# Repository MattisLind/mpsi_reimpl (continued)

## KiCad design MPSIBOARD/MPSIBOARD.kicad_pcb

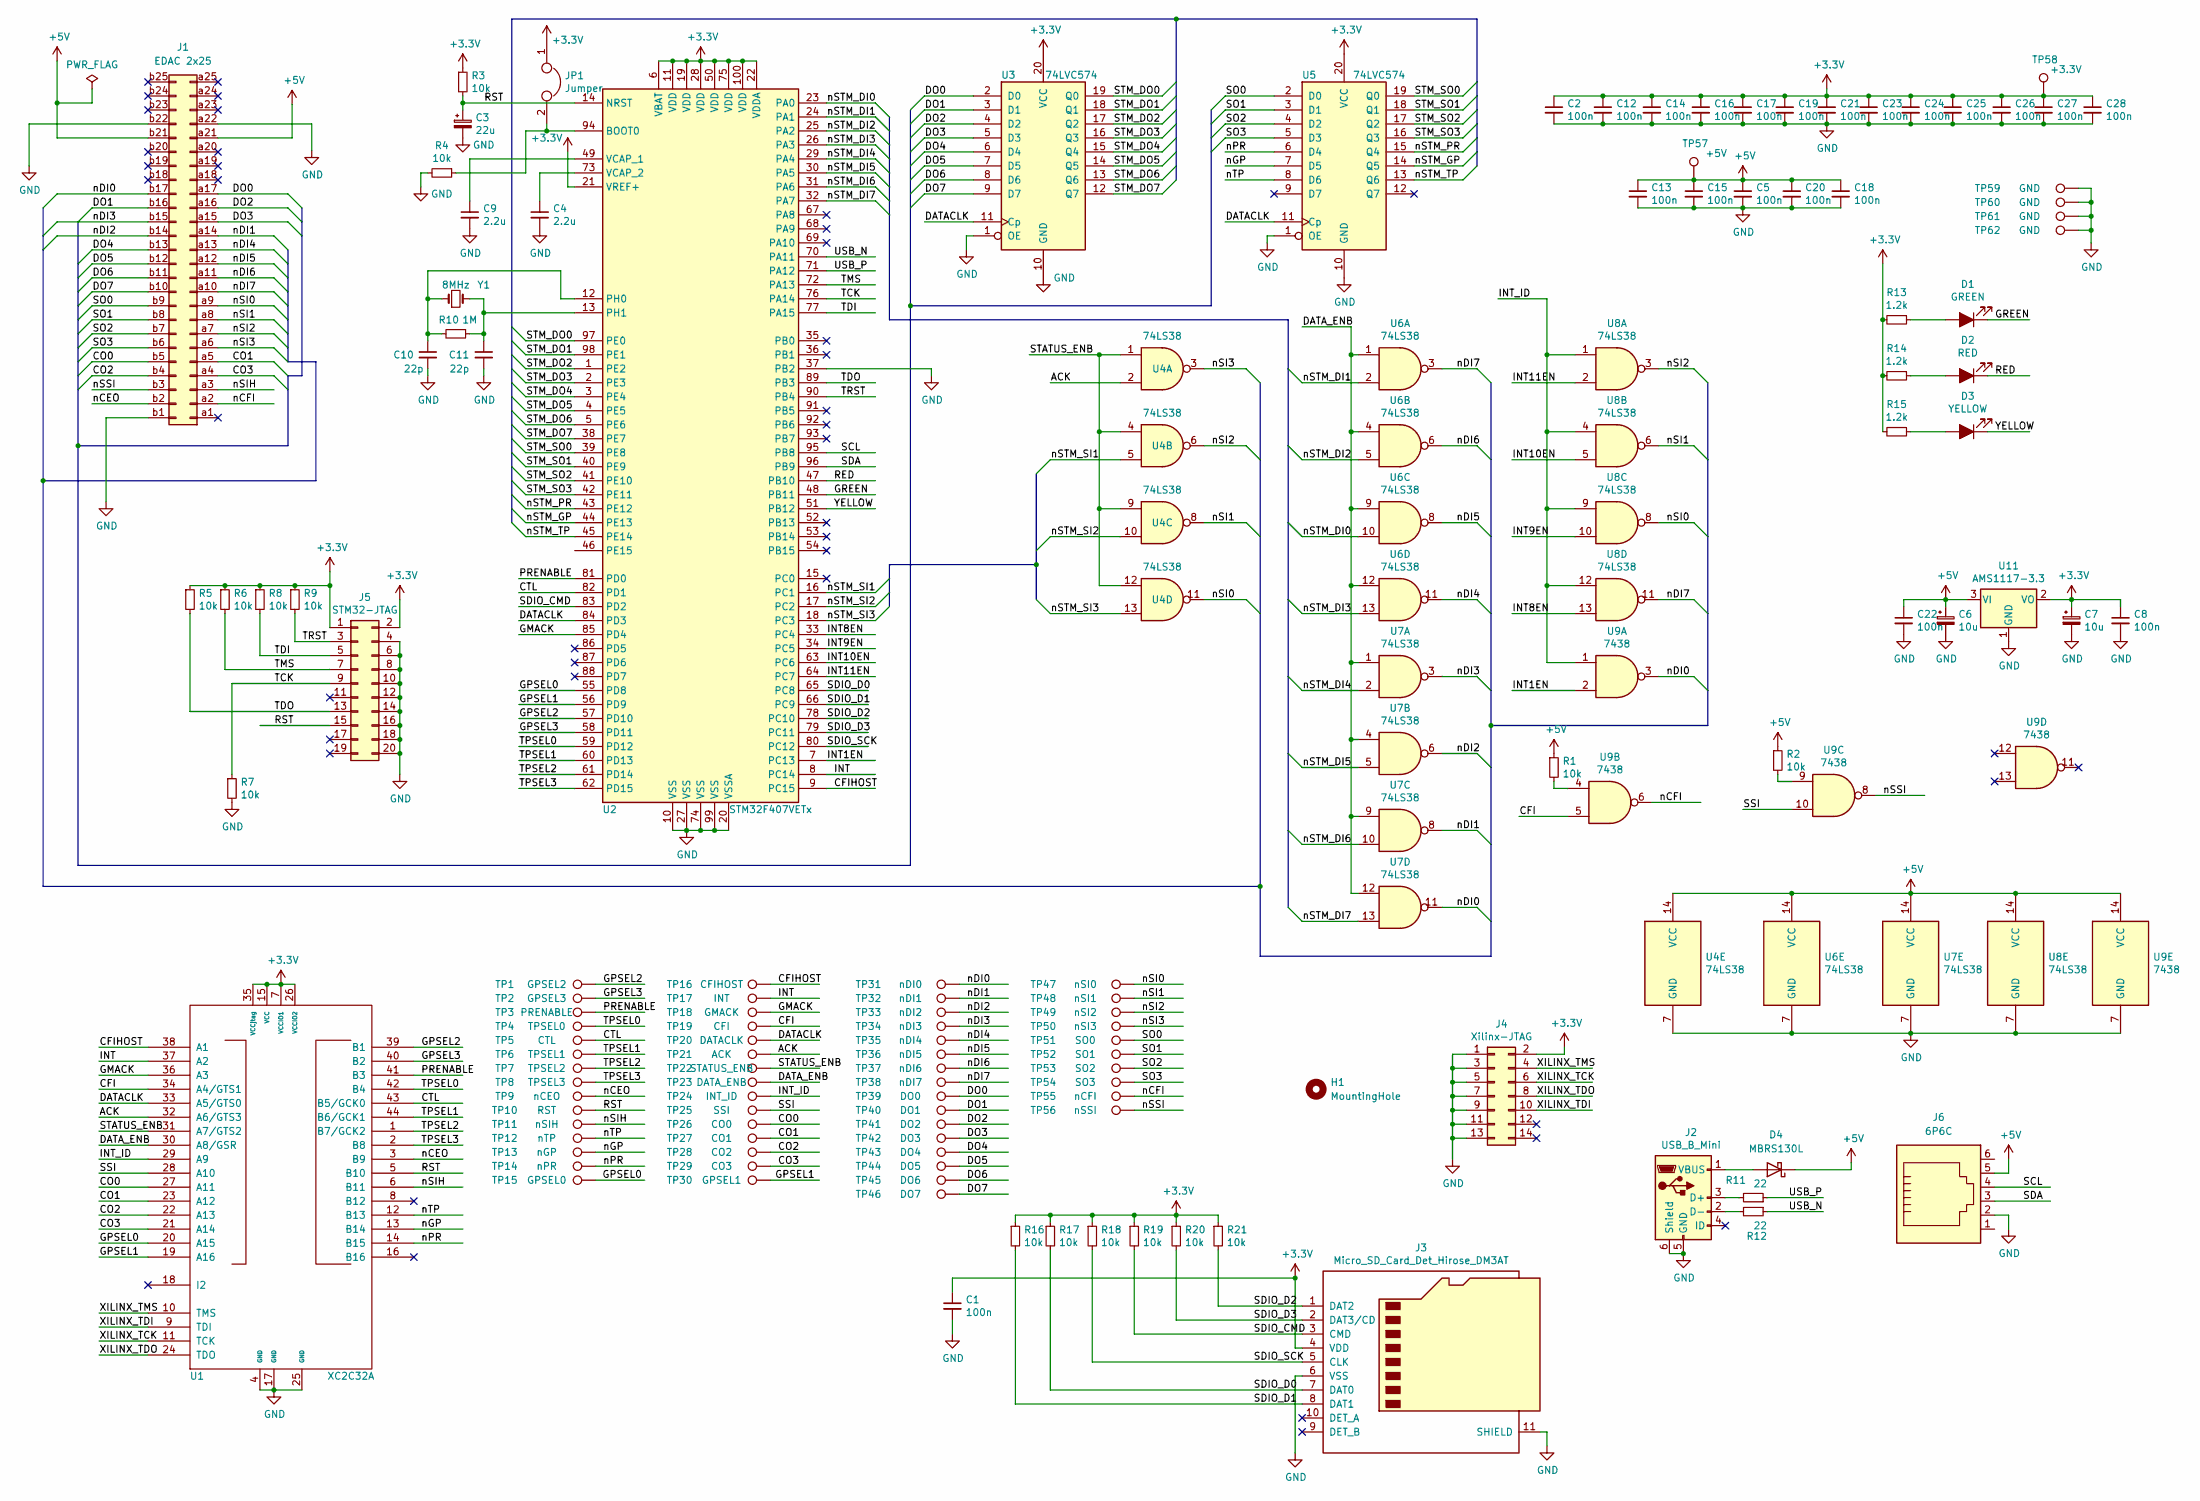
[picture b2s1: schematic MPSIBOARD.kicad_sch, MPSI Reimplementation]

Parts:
C1, C2, C5, C8, C12, C13, C14, C15, C16, C17, C18, C19, C20, C21, C22, C23, C24, C25, C26, C27, C28: 100n; C_0805_2012Metric
C3: 22u; CP_Elec_5x4.4
C4, C9: 2.2u; C_0805_2012Metric
C6, C7: 10u; CP_Elec_4x5.3
C10, C11: 22p; C_0805_2012Metric
D1: GREEN; LED_0805_2012Metric
D2: RED; LED_0805_2012Metric
D3: YELLOW; LED_0805_2012Metric
D4: MBRS130L; D_SMB
H1: MountingHole; MountingHole_3.2mm_M3
J1: EDAC 2x25; EDAC 2x25 3.96mm
J2: USB_B_Mini; USB_Mini-B_Lumberg_2486_01_Horizontal
J3: Micro_SD_Card_Det_Hirose_DM3AT; microSD_HC_Hirose_DM3AT-SF-PEJM5
J4: Xilinx-JTAG; IDC-Header_2x07_P2.54mm_Vertical
J5: STM32-JTAG; IDC-Header_2x10_P2.54mm_Vertical
J6: 6P6C; RJ12_Amphenol_54601
JP1: Jumper; PinHeader_1x02_P2.54mm_Vertical
R1, R2, R3, R4, R5, R6, R7, R8, R9, R16, R17, R18, R19, R20, R21: 10k; R_0805_2012Metric
R10: 1M; R_0805_2012Metric
R11, R12: 22; R_0805_2012Metric
R13, R14, R15: 1.2k; R_0805_2012Metric
TP1: GPSEL2; PinHeader_1x01_P2.54mm_Vertical
TP2: GPSEL3; PinHeader_1x01_P2.54mm_Vertical
TP3: PRENABLE; PinHeader_1x01_P2.54mm_Vertical
TP4: TPSEL0; PinHeader_1x01_P2.54mm_Vertical
TP5: CTL; PinHeader_1x01_P2.54mm_Vertical
TP6: TPSEL1; PinHeader_1x01_P2.54mm_Vertical
TP7: TPSEL2; PinHeader_1x01_P2.54mm_Vertical
TP8: TPSEL3; PinHeader_1x01_P2.54mm_Vertical
TP9: nCEO; PinHeader_1x01_P2.54mm_Vertical
TP10: RST; PinHeader_1x01_P2.54mm_Vertical
TP11: nSIH; PinHeader_1x01_P2.54mm_Vertical
TP12: nTP; PinHeader_1x01_P2.54mm_Vertical
TP13: nGP; PinHeader_1x01_P2.54mm_Vertical
TP14: nPR; PinHeader_1x01_P2.54mm_Vertical
TP15: GPSEL0; PinHeader_1x01_P2.54mm_Vertical
TP16: CFIHOST; PinHeader_1x01_P2.54mm_Vertical
TP17: INT; PinHeader_1x01_P2.54mm_Vertical
TP18: GMACK; PinHeader_1x01_P2.54mm_Vertical
TP19: CFI; PinHeader_1x01_P2.54mm_Vertical
TP20: DATACLK; PinHeader_1x01_P2.54mm_Vertical
TP21: ACK; PinHeader_1x01_P2.54mm_Vertical
TP22: STATUS_ENB; PinHeader_1x01_P2.54mm_Vertical
TP23: DATA_ENB; PinHeader_1x01_P2.54mm_Vertical
TP24: INT_ID; PinHeader_1x01_P2.54mm_Vertical
TP25: SSI; PinHeader_1x01_P2.54mm_Vertical
TP26: CO0; PinHeader_1x01_P2.54mm_Vertical
TP27: CO1; PinHeader_1x01_P2.54mm_Vertical
TP28: CO2; PinHeader_1x01_P2.54mm_Vertical
TP29: CO3; PinHeader_1x01_P2.54mm_Vertical
TP30: GPSEL1; PinHeader_1x01_P2.54mm_Vertical
TP31: nDI0; PinHeader_1x01_P2.54mm_Vertical
TP32: nDI1; PinHeader_1x01_P2.54mm_Vertical
TP33: nDI2; PinHeader_1x01_P2.54mm_Vertical
TP34: nDI3; PinHeader_1x01_P2.54mm_Vertical
TP35: nDI4; PinHeader_1x01_P2.54mm_Vertical
TP36: nDI5; PinHeader_1x01_P2.54mm_Vertical
TP37: nDI6; PinHeader_1x01_P2.54mm_Vertical
TP38: nDI7; PinHeader_1x01_P2.54mm_Vertical
TP39: DO0; PinHeader_1x01_P2.54mm_Vertical
TP40: DO1; PinHeader_1x01_P2.54mm_Vertical
TP41: DO2; PinHeader_1x01_P2.54mm_Vertical
TP42: DO3; PinHeader_1x01_P2.54mm_Vertical
TP43: DO4; PinHeader_1x01_P2.54mm_Vertical
TP44: DO5; PinHeader_1x01_P2.54mm_Vertical
TP45: DO6; PinHeader_1x01_P2.54mm_Vertical
TP46: DO7; PinHeader_1x01_P2.54mm_Vertical
TP47: nSI0; PinHeader_1x01_P2.54mm_Vertical
TP48: nSI1; PinHeader_1x01_P2.54mm_Vertical
TP49: nSI2; PinHeader_1x01_P2.54mm_Vertical
TP50: nSI3; PinHeader_1x01_P2.54mm_Vertical
TP51: SO0; PinHeader_1x01_P2.54mm_Vertical
TP52: SO1; PinHeader_1x01_P2.54mm_Vertical
TP53: SO2; PinHeader_1x01_P2.54mm_Vertical
TP54: SO3; PinHeader_1x01_P2.54mm_Vertical
TP55: nCFI; PinHeader_1x01_P2.54mm_Vertical
TP56: nSSI; PinHeader_1x01_P2.54mm_Vertical
TP57: +5V; PinHeader_1x01_P2.54mm_Vertical
TP58: +3.3V; PinHeader_1x01_P2.54mm_Vertical
TP59, TP60, TP61, TP62: GND; PinHeader_1x01_P2.54mm_Vertical
U1: XC2C32A; LQFP-44_10x10mm_P0.8mm
U2: STM32F407VETx; LQFP-100_14x14mm_P0.5mm
U3, U5: 74LVC574; TSSOP-20_4.4x6.5mm_P0.65mm
U4, U6, U7, U8: 74LS38; SO-14_5.3x10.2mm_P1.27mm
U9: 7438; SO-14_5.3x10.2mm_P1.27mm
U11: AMS1117-3.3; SOT-223-3_TabPin2
Y1: 8MHz; Crystal_SMD_HC49-SD

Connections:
+5V: C5.1, C6.1, C13.1, C15.1, C18.1, C20.1, C22.1, D4.1 (K), J1.a21, J1.b21, J6.5, R1.1, R2.1, TP57.1, U4.14 (VCC), U6.14 (VCC), U7.14 (VCC), U8.14 (VCC), U9.14 (VCC), U11.3 (VI)
/ACK: TP21.1, U1.32 (A6/GTS3), U4.2
/CFI: TP19.1, U1.34 (A4/GTS1), U9.5
/CFIHOST: TP16.1, U1.38 (A1), U2.9 (PC15)
/CO0: J1.b5, TP26.1, U1.27 (A11)
/CO1: J1.a5, TP27.1, U1.23 (A12)
/CO2: J1.b4, TP28.1, U1.22 (A13)
/CO3: J1.a4, TP29.1, U1.21 (A14)
/CTL: TP5.1, U1.43 (B5/GCK0), U2.82 (PD1)
/DATACLK: TP20.1, U1.33 (A5/GTS0), U2.84 (PD3), U3.11 (Cp), U5.11 (Cp)
/DATA_ENB: TP23.1, U1.30 (A8/GSR), U6.1, U6.4, U6.9, U6.12, U7.1, U7.4, U7.9, U7.12
/DO0: J1.a17, TP39.1, U3.2 (D0)
/DO1: J1.b16, TP40.1, U3.3 (D1)
/DO2: J1.a16, TP41.1, U3.4 (D2)
/DO3: J1.a15, TP42.1, U3.5 (D3)
/DO4: J1.b13, TP43.1, U3.6 (D4)
/DO5: J1.b12, TP44.1, U3.7 (D5)
/DO6: J1.b11, TP45.1, U3.8 (D6)
/DO7: J1.b10, TP46.1, U3.9 (D7)
/GMACK: TP18.1, U1.36 (A3), U2.85 (PD4)
/GPSEL0: TP15.1, U1.20 (A15), U2.55 (PD8)
/GPSEL1: TP30.1, U1.19 (A16), U2.56 (PD9)
/GPSEL2: TP1.1, U1.39 (B1), U2.57 (PD10)
/GPSEL3: TP2.1, U1.40 (B2), U2.58 (PD11)
/GREEN: D1.1 (K), U2.48 (PB11)
/INT: TP17.1, U1.37 (A2), U2.8 (PC14)
/INT1EN: U2.7 (PC13), U9.2
/INT8EN: U2.33 (PC4), U8.13
/INT9EN: U2.34 (PC5), U8.10
/INT10EN: U2.63 (PC6), U8.5
/INT11EN: U2.64 (PC7), U8.2
/INT_ID: TP24.1, U1.29 (A9), U8.1, U8.4, U8.9, U8.12, U9.1
/PRENABLE: TP3.1, U1.41 (B3), U2.81 (PD0)
/RED: D2.1 (K), U2.47 (PB10)
/RST: C3.1, J5.15, R3.2, TP10.1, U1.5 (B10), U2.14 (NRST)
/SCL: J6.4, U2.95 (PB8)
/SDA: J6.3, U2.96 (PB9)
/SDIO_CMD: J3.3 (CMD), R19.2, U2.83 (PD2)
/SDIO_D0: J3.7 (DAT0), R17.2, U2.65 (PC8)
/SDIO_D1: J3.8 (DAT1), R16.2, U2.66 (PC9)
/SDIO_D2: J3.1 (DAT2), R21.2, U2.78 (PC10)
/SDIO_D3: J3.2 (DAT3/CD), R20.2, U2.79 (PC11)
/SDIO_SCK: J3.5 (CLK), R18.2, U2.80 (PC12)
/SO0: J1.b9, TP51.1, U5.2 (D0)
/SO1: J1.b8, TP52.1, U5.3 (D1)
/SO2: J1.b7, TP53.1, U5.4 (D2)
/SO3: J1.b6, TP54.1, U5.5 (D3)
/SSI: TP25.1, U1.28 (A10), U9.10
/STATUS_ENB: TP22.1, U1.31 (A7/GTS2), U4.1, U4.4, U4.9, U4.12
/STM_DO0: U2.97 (PE0), U3.19 (Q0)
/STM_DO1: U2.98 (PE1), U3.18 (Q1)
/STM_DO2: U2.1 (PE2), U3.17 (Q2)
/STM_DO3: U2.2 (PE3), U3.16 (Q3)
/STM_DO4: U2.3 (PE4), U3.15 (Q4)
/STM_DO5: U2.4 (PE5), U3.14 (Q5)
/STM_DO6: U2.5 (PE6), U3.13 (Q6)
/STM_DO7: U2.38 (PE7), U3.12 (Q7)
/STM_SO0: U2.39 (PE8), U5.19 (Q0)
/STM_SO1: U2.40 (PE9), U5.18 (Q1)
/STM_SO2: U2.41 (PE10), U5.17 (Q2)
/STM_SO3: U2.42 (PE11), U5.16 (Q3)
/TCK: J5.9, R7.1, U2.76 (PA14)
/TDI: J5.5, R8.2, U2.77 (PA15)
/TDO: J5.13, R5.2, U2.89 (PB3)
/TMS: J5.7, R6.2, U2.72 (PA13)
/TPSEL0: TP4.1, U1.42 (B4), U2.59 (PD12)
/TPSEL1: TP6.1, U1.44 (B6/GCK1), U2.60 (PD13)
/TPSEL2: TP7.1, U1.1 (B7/GCK2), U2.61 (PD14)
/TPSEL3: TP8.1, U1.2 (B8), U2.62 (PD15)
/TRST: J5.3, R9.2, U2.90 (PB4)
/USB_N: R12.1, U2.70 (PA11)
/USB_P: R11.1, U2.71 (PA12)
/XILINX_TCK: J4.6, U1.11 (TCK)
/XILINX_TDI: J4.10, U1.9 (TDI)
/XILINX_TDO: J4.8, U1.24 (TDO)
/XILINX_TMS: J4.4, U1.10 (TMS)
/YELLOW: D3.1 (K), U2.51 (PB12)
/nCEO: J1.b2, TP9.1, U1.3 (B9)
/nCFI: J1.a2, TP55.1, U9.6
/nDI0: J1.b17, TP31.1, U7.11, U9.3
/nDI1: J1.a14, TP32.1, U7.8
/nDI2: J1.b14, TP33.1, U7.6
/nDI3: J1.b15, TP34.1, U7.3
/nDI4: J1.a13, TP35.1, U6.11
/nDI5: J1.a12, TP36.1, U6.8
/nDI6: J1.a11, TP37.1, U6.6
/nDI7: J1.a10, TP38.1, U6.3, U8.11
/nGP: TP13.1, U1.13 (B14), U5.7 (D5)
/nPR: TP14.1, U1.14 (B15), U5.6 (D4)
/nSI0: J1.a9, TP47.1, U4.11, U8.8
/nSI1: J1.a8, TP48.1, U4.8, U8.6
/nSI2: J1.a7, TP49.1, U4.6, U8.3
/nSI3: J1.a6, TP50.1, U4.3
/nSIH: J1.a3, TP11.1, U1.6 (B11)
/nSSI: J1.b3, TP56.1, U9.8
/nSTM_DI0: U2.23 (PA0), U6.10
/nSTM_DI1: U2.24 (PA1), U6.2
/nSTM_DI2: U2.25 (PA2), U6.5
/nSTM_DI3: U2.26 (PA3), U6.13
/nSTM_DI4: U2.29 (PA4), U7.2
/nSTM_DI5: U2.30 (PA5), U7.5
/nSTM_DI6: U2.31 (PA6), U7.10
/nSTM_DI7: U2.32 (PA7), U7.13
/nSTM_GP: U2.44 (PE13), U5.14 (Q5)
/nSTM_PR: U2.43 (PE12), U5.15 (Q4)
/nSTM_SI1: U2.16 (PC1), U4.5
/nSTM_SI2: U2.17 (PC2), U4.10
/nSTM_SI3: U2.18 (PC3), U4.13
/nSTM_TP: U2.45 (PE14), U5.13 (Q6)
/nTP: TP12.1, U1.12 (B13), U5.8 (D6)
GND: C1.2, C2.2, C3.2, C4.2, C5.2, C6.2, C7.2, C8.2, C9.2, C10.2, C11.2, C12.2, C13.2, C14.2, C15.2, C16.2, C17.2, C18.2, C19.2, C20.2, C21.2, C22.2, C23.2, C24.2, C25.2, C26.2, C27.2, C28.2, J1.a22, J1.b1, J1.b22, J2.5 (GND), J2.6 (Shield), J3.6 (VSS), J3.11 (SHIELD), J4.1, J4.3, J4.5, J4.7, J4.9, J4.11, J4.13, J5.4, J5.6, J5.8, J5.10, J5.12, J5.14, J5.16, J5.18, J5.20, J6.2, R4.2, R7.2, TP59.1, TP60.1, TP61.1, TP62.1, U1.4 (GND), U1.17 (GND), U1.25 (GND), U2.10 (VSS), U2.20 (VSSA), U2.27 (VSS), U2.37 (PB2), U2.74 (VSS), U2.99 (VSS), U3.1 (OE), U3.10 (GND), U4.7 (GND), U5.1 (OE), U5.10 (GND), U6.7 (GND), U7.7 (GND), U8.7 (GND), U9.7 (GND), U11.1 (GND)
unnamed: C4.1, U2.73 (VCAP_2)
unnamed: C9.1, U2.49 (VCAP_1)
unnamed: C10.1, R10.2, U2.12 (PH0), Y1.1
unnamed: C11.1, R10.1, U2.13 (PH1), Y1.2
unnamed: D1.2 (A), R13.1
unnamed: D2.2 (A), R14.1
unnamed: D3.2 (A), R15.1
unnamed: D4.2 (A), J2.1 (VBUS)
unnamed: J2.2 (D-), R12.2
unnamed: J2.3 (D+), R11.2
unnamed: JP1.2, R4.1, U2.94 (BOOT0)
unnamed: R1.2, U9.4
unnamed: R2.2, U9.9

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
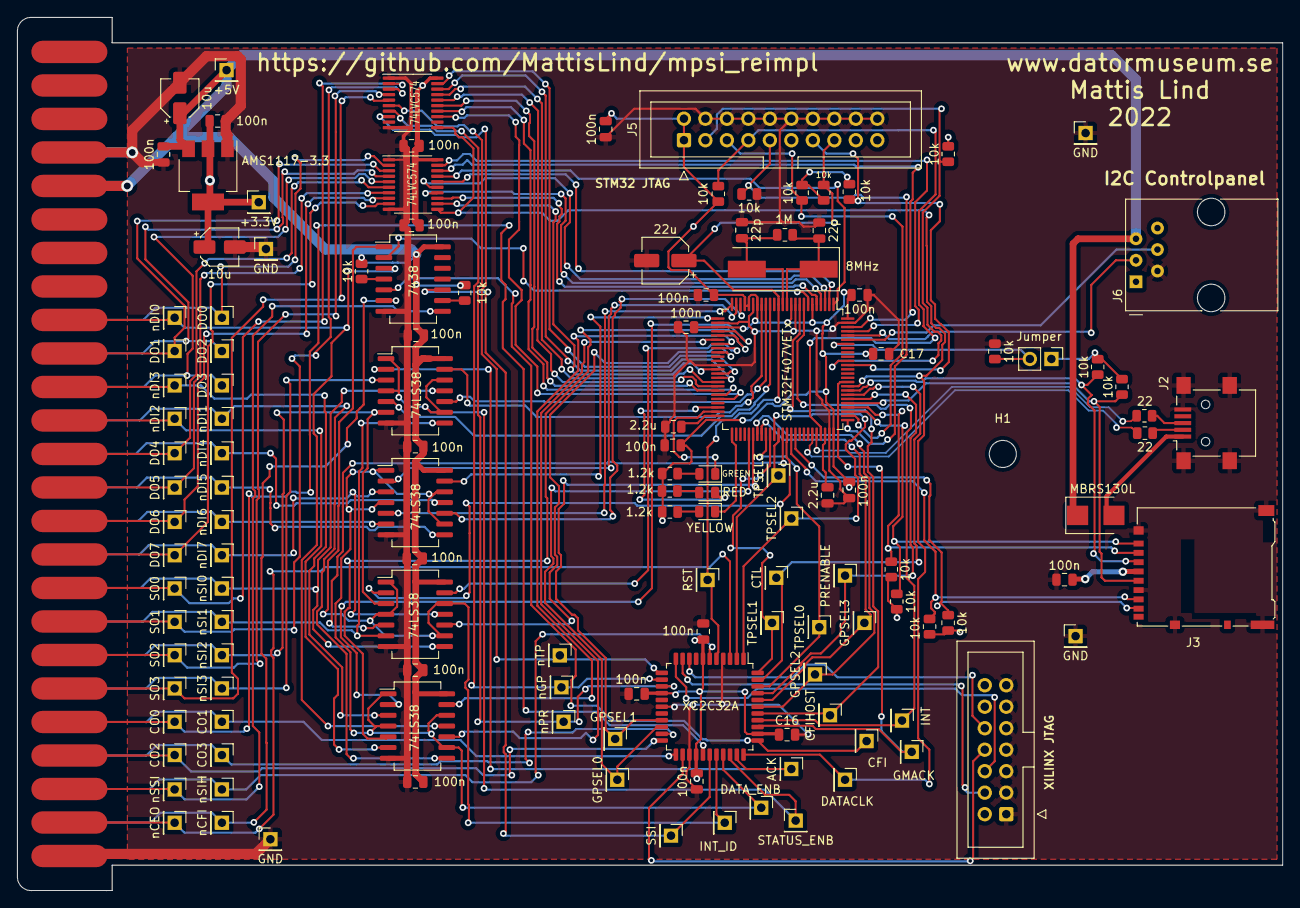
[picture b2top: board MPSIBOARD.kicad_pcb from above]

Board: 2 copper layers, 149.5 x 103.2 mm, 134 parts (0 on the bottom side), 125 nets.

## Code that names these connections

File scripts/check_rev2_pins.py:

#!/usr/bin/env python3
"""Cross-check package pins, inline fitter constraints and exported KiCad nets."""
import argparse
import json
from pathlib import Path
import re
from kicad_sexpr import read, child, children

ROOT = Path(__file__).resolve().parents[1]
MAP = json.loads((ROOT / 'hardware/rev2/pinmap.json').read_text())
SPECIAL = {'VCC', 'GND', 'TDI', 'TMS', 'TCK', 'TDO'}


def main():
    parser = argparse.ArgumentParser(description=__doc__)
    parser.add_argument('--fit', type=Path)
    parser.add_argument('--netlist', type=Path)
    parser.add_argument('--board', type=Path, help='also compare PCB pad nets to the exported netlist')
    args = parser.parse_args()
    ports = {name:int(pin) for pin,(name,net) in MAP['cpld'].items()
             if name not in SPECIAL and not name.startswith('SPARE')}
    source = (ROOT / 'hardware/rev2/rtl/mpsi_cpld.vhdl').read_text()
    inline = {name:int(pin) for name,pin in re.findall(r'^--PIN: (\w+) : (\d+)$', source, re.M)}
    jtag = {name:int(pin) for pin,(name,net) in MAP['cpld'].items() if name in ('TDI','TMS','TCK','TDO')}
    assert inline == ports | jtag, 'VHDL --PIN constraints disagree with pinmap.json'
    assert len(ports) == len(set(ports.values())) == 29, 'duplicate/missing CPLD pins'
    assert ports['reset_n'] == 1 and ports['hp_run'] == 44
    assert {ports['mck'],ports['spi_sck'],ports['spi_cs_n']} == {43,2,41}, 'global clock pins'
    assert {p for p,v in MAP['cpld'].items() if v[0]=='VCC'} == {'3','15','23','35'}
    assert {p for p,v in MAP['cpld'].items() if v[0]=='GND'} == {'10','22','30','42'}
    assert {p for p,v in MAP['cpld'].items() if v[0] in ('TDI','TMS','TCK','TDO')} == {'7','13','32','38'}
    assert {v[0] for v in MAP['mcu'].values() if v[2]=='in_5v_ft'} == {'PB14','PB10'}
    assert MAP['mcu']['30'][0:2] == ['PA9','DEBUG_TX']
    assert MAP['mcu']['31'][0:2] == ['PA10','DEBUG_RX']
    print('PASS: 29 CPLD constraints, global clocks/JTAG/supplies, FT inputs and USART1 reservation')
    if args.fit:
        fitted = {name:int(pin) for name,pin in re.findall(r'^\s*(\w+)\s*:\s*(\d+)', args.fit.read_text(), re.M) if name in ports}
        assert fitted == ports, 'fitter changed or omitted requested package pins'
        jed = args.fit.with_suffix('.jed')
        assert jed.is_file() and jed.stat().st_size > 0, 'no JEDEC generated'
        report = args.fit.with_suffix('.fit').read_text()
        assert '$Device PLCC44 fits; JTAG ON;' in report, 'fitter did not report a fit with JTAG'
        assert re.search(r'Pin-Keeper\s*=\s*OFF', report), 'pin keepers must be disabled'
        hp = {name:pin for name,pin in ports.items() if name.startswith('hp_n_')}
        open_collector = {name:int(pin) for pin,name in re.findall(
            r'^MC\d+\s+(\d+)\s+.*?\b(hp_n_\w+)\b.*\sfo\s*$', report, re.M)}
        assert open_collector == hp, 'HP outputs were not all fitted open collector'
        mapped = len(re.findall(r'\(cellRef DFF\w*', args.fit.with_suffix('.edif').read_text()))
        fitted_registers = re.search(r'Total Flip-Flop used\s+(\d+)/64', report)
        assert fitted_registers and int(fitted_registers[1]) == mapped, 'fitter lost registers'
        print(f'PASS: retained pins, JEDEC, JTAG, 14 open-collector HP outputs, no keepers, {mapped} registers')
    if args.netlist:
        tree = read(args.netlist)
        nets, pins = {}, {}
        for net in children(child(tree,'nets'),'net'):
            name = child(net,'name')[1]
            nodes = {(child(n,'ref')[1],child(n,'pin')[1]) for n in children(net,'node')}
            nets[name] = nodes
            pins.update({node:name for node in nodes})
        for ref, mapping in [('U1',{p:v[1] for p,v in MAP['mcu'].items()}),
                             ('U2',{p:v[1] for p,v in MAP['cpld'].items()}),
                             ('J1',MAP['connector']),
                             ('J5',{str(i):v for i,v in enumerate(MAP['debug_header'],1)})]:
            for pin,net in mapping.items():
                actual = pins.get((ref,pin))
                if net is None:
                    assert actual is None or actual.startswith('unconnected-'), f'{ref}.{pin} should be NC'
                else:
                    assert actual == net, f'{ref}.{pin}: expected {net}, got {actual}'
        expected = {
          'HP_SPI_SCK': {('U1','26'),('U2','2'),('U3','2'),('U4','2')},
          'HP_SPI_MISO': {('U1','27'),('U4','9')},
          'SHIFT_CHAIN': {('U3','9'),('U4','10')},
          'HP_INPUT_PL_n': {('U2','31'),('U3','1'),('U4','1')},
          'CPLD_MCK': {('U1','29'),('U2','43')},
          'USB_CONN_DM': {('J2','5'),('J2','7'),('U5','6')},
          'USB_CONN_DP': {('J2','6'),('J2','8'),('U5','4')},
          'USB_ESD_DM': {('U5','1'),('R21','2')},
          'USB_ESD_DP': {('U5','3'),('R22','2')},
          'USB_DM': {('U1','32'),('R21','1')},
          'USB_DP': {('U1','33'),('R22','1'),('R23','2')},
          'USB_PULLUP_EN': {('U1','41'),('R23','1'),('R24','1')},
          'USB_CC1': {('J2','4'),('R19','1')},
          'USB_CC2': {('J2','10'),('R20','1')},
          'SD_CD_n': {('U1','40'),('J3','10'),('R8','1')},
          'GND': {('J3','SH'),('U6','3'),('U6','7')},
          '+3V3': {('U6','1')}, '+5V_LOGIC': {('U6','6'),('U6','4')}
        }
        for name,nodes in expected.items():
            assert nodes <= nets[name], f'missing/miswired connection on {name}'
        for bit,pin in enumerate(['11','12','13','14','3','4','5','6']):
            assert pins[('U3',pin)] == 'DO'+str(bit), 'lower HCT165 byte order'
            assert pins[('U4',pin)] == ('SO'+str(bit) if bit < 4 else 'CO'+str(bit-4)), 'upper HCT165 word order'
        print('PASS: KiCad MCU/CPLD/connector/debug pins, HCT165 word order, USB protection and SD detect')
        if args.board:
            board = read(args.board)
            count = 0
            for footprint in children(board, 'footprint'):
                ref = next(p[2] for p in children(footprint,'property') if p[1]=='Reference')
                for pad in children(footprint,'pad'):
                    if not pad[1]: continue # mounting hole
                    actual = child(pad,'net')
                    actual = actual[-1] if actual else None
                    assert actual == pins.get((ref,pad[1])), f'PCB {ref}.{pad[1]}: {actual} != schematic'
                    count += 1
            print(f'PASS: {count} PCB pads match schematic nets, including NC and shield pads')
    elif args.board:
        parser.error('--board requires --netlist')


if __name__ == '__main__':
    main()

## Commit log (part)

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2019-08-22 Initial version of README
2019-08-22 Spelling
2019-10-21 Added WinCUPL code that does all the various logic
2019-10-21 Added the source code by Brint Hilpert
2019-10-21 Initial README.md
2021-01-21 Added VHDL source for XC2C32A CPLD since it easier to work with decently modern tools than WinCUPL which is just too old.
2021-01-21 New design idea.
2021-04-05 Added schematic.
2021-04-05 Add .png
2021-04-05 Add schematic
2021-04-08 Added three more outputs.
2021-04-25 Some updates of schematic.
2023-01-06 A layout done.
